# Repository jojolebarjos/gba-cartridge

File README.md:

# GameBoy Advance cartridge

This project is about making homebrew cartridges for the GameBoy Advance, using an FPGA (here a [TinyFPGA](https://tinyfpga.com/) BX).
Given the update frequency (and the fact that both falling-edges and rising-edges are meaningful), this is more convenient than bit-banging using some micro-controller.
A few experiments are available, some making use of an additional micro-controller (here an [Arduino Nano 33 BLE](https://store.arduino.cc/products/arduino-nano-33-ble)) for communication.

## Cartridge protocol

The cartridge has the following pins:

 * 1: `VCC`, at 3.3V.
 * 2: `PHI`, the physical clock, which can be configured (disabled, 4.19MHz, 8.38MHz, 16.78MHz). Disabled by default. See [waitstate control](https://www.akkit.org/info/gbatek.htm#gbasystemcontrol).
 * 3: `~WR`, write control.
 * 4: `~RD`, read control.
 * 5: `~CS`, select ROM.
 * 6-21: `AD`, address and data.
 * 22-29: `A`, address or data.
 * 30: `CS2`, select SRAM.
 * 31: `IRQ`, interrupt request. Can be left unconnected or grounded.
 * 32: `GND`, ground.

General comments about memory accesses:

 * Data format is always little endian, i.e. least significant byte is first.
 * Depending on the requested (virtual) address and operation, the GameBoy will either assume ROM or RAM when accessing the cartridge.
 * ROM data access is 16-bits, hence data is aligned on 2-bytes steps. This means the implicit least-significant bit of the address is always 0 (i.e. `A0..23` is the address divided by 2).
 * ARM instructions (32-bits) are slow to fetch. It is better to use THUMB instructions, or copy the code in WRAM.
 * GamePak accesses can be either sequential or non-sequential. The first access to a random location in ROM must be non-sequential.
 * The GameBoy will wait a few cycles when accessing memory. Up to 3 configurations can be used (useful if the cartridge has multiple ROM units with different physical properties). By default, it will assume 4 cycles for random access, and then 2 cycles for sequential access. See [waitstate control](https://www.akkit.org/info/gbatek.htm#gbasystemcontrol).
 * When doing ROM access, the `AD` bus is used in both direction. The cartridge should actively write only when both `~CS` and `~RD` are low.
 * When doing RAM access, the `AD` bus is used for the 16-bits address, and the 8-bits data is returned through `A16..23`. `~CS2` is used instead of `~CS`.

A read access from the ROM is done as follows:

 * On `~CS` falling-edge, the cartridge latches A0-A23 as address.
 * On `~RD` falling-edge, the cartridge fetches the data at latched address and outputs D0-D15. The output must be ready by next rising-edge of `~RD` (depends on waitstates).
 * On `~RD` rising-edge, the cartridge increments latched address by one (i.e. allow sequential read by just strobing `~RD`).
 * On `~CS` rising-edge, the transaction is done.

While it usually makes no sense to write to a ROM, the GameBoy will submit write commands in a similar fashion, toggling `~WR` instead.
In this project, we use that to let the software write back to the cartridge, for instance to report key input.

Therefore, a simple read-only GamePak ROM does not use `PHI`, `~WR`, `~CS2` and `IRQ`.

Cartridges that require more than 64K of storage will need to use bank switching to map more memory.
This topic has not been investigated in this project.

Relevant links:

 * References
   * https://github.com/gbadev-org/awesome-gbadev
   * https://www.gbadev.org/
   * https://www.akkit.org/info/gbatek.htm
   * https://problemkaputt.de/gbatek.htm
   * http://www.hardwarebook.info/Game_Pak
 * Blogs and websites
   * https://gekkio.fi/
     * https://gekkio.fi/files/gb-docs/gbctr.pdf
     * https://github.com/gekkio/gb-hardware
   * https://www.darkfader.net/gba/
     * http://files.darkfader.net/gba/files/cartridge.txt
   * https://reinerziegler.de.mirrors.gg8.se/GBA/gba.htm
   * http://kylehalladay.com/blog/tutorial/gba/2017/04/18/GBA-By-Example-4.html
   * https://fabiensanglard.net/another_world_polygons_GBA/
   * https://github.com/PeterLemon/GBA
 * Custom cartridges
   * https://github.com/uXeBoy/GBA
   * https://github.com/uXeBoy/GBArduboy
   * http://www.dl9sec.de/prj_gbacart.html
 * Cartridge reader
   * https://www.insidegadgets.com/2011/03/19/gbcartread-arduino-based-gameboy-cart-reader-%E2%80%93-part-1-read-the-rom/
   * https://douevenknow.us/post/68126856498/arduino-based-gba-rom-dumper-part-1
   * https://dragaosemchama.com/en/2015/12/gameboy-pak-reader-cartridge-header/
   * https://mgba.io/2015/10/20/dumping-the-undumped/
 * Multiboot-based
   * https://github.com/Shyri/gba-bt-hid
 * Old GameBoy, but still very interesting
   * https://dhole.github.io/post/gameboy_cartridge_emu_1/
   * https://retrocomputing.stackexchange.com/questions/11732/how-does-the-gameboys-memory-bank-switching-work
   * https://github.com/dwaq/Homebrew-Gameboy-Cartridge
   * https://www.insidegadgets.com/2018/04/18/building-a-2mb-mbc5-gameboy-cart-part-1-cpld-as-the-mbc-and-adding-flash-as-our-rom/
   * http://bitwise.bperki.com/2018/08/08/custom-game-boy-cartridge-project-update-1/
   * https://wiki.tauwasser.eu/view/MBC1
   * https://catskull.net/gameboy-boot-screen-logo.html

## Compiling a GameBoy Advance game

The GameBoy Advance features an ARM-based processor.
We will use [devkitPro](https://devkitpro.org/wiki/Main_Page) to compile binaries.

The most straightforward approach is to use the [Docker image](https://github.com/devkitPro/docker).
We share the local folder with the container, to avoid unnecessary copies.

```
# Run in interactive mode
docker run -ti -v ${PWD}:/rom devkitpro/devkitarm
# On Windows: docker run -ti -v %cd%:/rom devkitpro/devkitarm

# Add compiler binaries to path
export PATH="/opt/devkitpro/devkitARM/bin/:$PATH"

# Go to shared folder and build files
cd /rom/
make
```

Links related to GBA software development:

 * https://www.coranac.com/tonc/text/toc.htm
 * https://devkitpro.org/wiki/Getting_Started
 * https://github.com/devkitPro/docker
 * https://github.com/devkitPro/gba-examples
 * http://kylehalladay.com/blog/tutorial/gba/2017/03/28/GBA-By-Example-1.html
 * https://www.coranac.com/tonc/text/setup.htm#sec-dkp
 * https://www.akkit.org/info/gbatek.htm#gbakeypadinput
 * https://www.coranac.com/tonc/text/keys.htm
 * https://github.com/felixjones/gba-plusplus

Emulators and GameBoy implementations:

 * https://mgba.io/
 * https://github.com/RobertPeip/FPGBA
 * https://github.com/AntonioND/giibiiadvance
 * https://mitxela.com/projects/swotgb/about

## Development PCB

In order to have a flexible playground, a custom-made PCB has been designed using [KiCad](https://www.kicad.org/) and ordered on [JLCPCB](https://jlcpcb.com/).
[This](https://www.aliexpress.com/item/1005003412771520.html) cheap cartridge header can be soldered to connect an actual cartridge, if needed.
A simple casing has been designed using [FreeCAD](https://www.freecadweb.org/) and 3D-printed (resin) to properly fit the GameBoy Advance.
Depending on whether a GameBoy Advance and/or a cartridge is used, the FPGA can have various roles.

 * The 32 pins of the cartridge are forwarded from the GameBoy to the cartridge.
 * Two sets of connectors are available to intercept (or drive) the pins: a 2x16 header for generic usage, and a 2x14 header designed to hold the TinyFPGA BX.
 * A dedicated header is available to configure power supply.
 * `A` is not exposed to the TinyFPGA BX, as there are not enough pins. Note that some GPIO pins are exposed as pads by the FPGA, but this is not convenient for this project.
 * Instead, some pins are exposed as "extra", and can be used either for external communication (e.g. SPI) or connected to `A` to extend the address space.
 * Use ENIG finish (i.e. *not* HASL), for more strength.
 * In order to fit in the opening, a thickness of 0.8mm should be used (as the casing already takes roughly 1mm).

See the [schema](pcb.sch.pdf) for more details.

## Getting started with TinyFPGA BX

As described in the [User Guide](https://tinyfpga.com/bx/guide.html), install [APIO](https://github.com/FPGAWARS/apio):

```
conda create -n fpga python=3.7
activate fpga
pip install apio==0.4.0b5 tinyprog
apio install system scons icestorm iverilog
```

Connect the board and run:

```
apio install drivers
apio drivers --serial-enable
```

Reconnect the board, and check that the device is recognized.
Windows might take a few seconds to actually detect and properly setup the serial device.

```
apio system --lsserial
```

Make sure the board is up-to-date:

```
tinyprog --update-bootloader
```

For better integration, use [Atom](https://atom.io/) and install the `apio-ide` package.
Note that you should run Atom inside the Conda environment, so that paths are properly set up:

```
atom --new-instance
```

Using the [default template](https://github.com/tinyfpga/TinyFPGA-BX/tree/master/apio_template), you can quickly start developing the TinyFPGA.

Note that you can upload the code by calling `tinyprog` directly:

```
tinyprog --program hardware.bin
```

The `apio-ide` package provide shortcuts for the most common operations, i.e. build and program.
Use `F8` to show the compilation log after a successful build.

Links:

 * https://tinyfpga.com/
 * http://www.clifford.at/icestorm/
 * https://www.youtube.com/watch?v=ZNunxg7o8l0
 * https://hackaday.io/project/159191-fpga-bootcamp-1
 * https://github.com/YosysHQ/nextpnr

## Experiments

A few simple experiments have been made until now.

### Cartridge dump

An Arduino Nano 33 BLE is connected to a TinyFPGA BX over SPI.

| Name | Arduino Nano 33 BLE | Wire | Board | TinyFPGA BX |
| ---- | ---- | ---- | ---- | ---- |
| GND | GND | black | GND | GND | GND |
| MISO | D2 (2) | green | EXT0 | 1 (A2) |
| MOSI | D3 (3) | blue | EXT1 | 2 (A1) |
| SCK | D4 (4) | white | EXT2 | 3 (B1) |
| SS | D5 (5) | yellow | EXT3 | 4 (C2) |

The cartridge is powered by the TinyFPGA BX, i.e. `VCC_CART` is connected to `VOUT`.

This is a naive implementation of the above-mentioned protocol:

 * The FPGA toggles `~CS` and `~RD`, writes the address and reads the output through `AD`. Note that, as `A` is ignored, only the first 131072 can be read.
 * The Arduino acts as a bridge, communicating with the FPGA using SPI and with the computer using USB.
 * A Python script sends the commands and dumps the content to a binary file.

Note that this approach does not handle any memory bank.
Therefore, it cannot be used as-is to dump a whole cartridge.

See [`./experiments/dump/`](./dump/) for more details.

### Read-only cartridge

The TinyFPGA BX acts as a read-only ROM cartridge.
A simple "game" is provided, where a white dot is moved using the arrows.

See [`./experiments/read/`](./read/) for more details.

### Read-write

The TinyFPGA BX acts as a writable ROM cartridge.
A simple "game" is provided, where buttons are written at each frame to the cartridge memory.

See [`./experiments/write/`](./write/) for more details.

### USB gamepad

The TinyFPGA BX acts as a writable ROM cartridge.
A simple "game" is provided, where buttons are written at each frame to the cartridge memory.
This information is then forwarded to an Arduino Nano 33 BLE, which is recognized as a HID gamepad.

TODO: use HID over USB/BLE

TODO: use interrupts on GBA (and sleep when no button is pressed)

TODO: make FPGA the SPI master, or use interrupts to let the Arduino communicate only when needed

See [`./experiments/gamepad/`](./gamepad/) for more details.

### Direct Memory Access

...

http://problemkaputt.de/gbatek-gba-dma-transfers.htm
https://gbdev.gg8.se/wiki/articles/Video_Display
https://austinjadams.com/blog/autograding-gba-dma/
https://badd10de.dev/notes/gba-programming.html

See [`./experiments/dma/`](./dma/) for more details.

### VGA

The GBA has a TFT color LCD that is 240 x 160 pixels in size and has a refresh rate of exactly 280896 cpu cycles per frame, or around 59.73 hz.
Most GBA programs will need to structure themselves around this refresh rate.
The LCD can display 15-bit RGB colors (0bxbbbbbgggggrrrrr).

TODO:
 * Use backbuffer (with palette) mode 4, to acquire next frame during previous one is drawn
 * VGA is an analog signal, with 5 (+GND) relevant pins: R, G, B, H-Sync, V-Sync
 * We can naively connect these to digital inputs, effectively displaying only 8 colors
 * We can also use an analog-to-digital serial converter, if FPGA is fast enough
 * https://electronics.stackexchange.com/questions/134674/how-vga-monitor-detects-video-resolution
 * Need 3:2 resolution, so maybe use 320x200 and trim 20 pixels horizontally? https://www.videotechnology.com/0904/formats.html

The closest standard mode is 720x480 @60Hz RGB 4:4:4

 * https://en.wikipedia.org/wiki/Video_Graphics_Array
 * https://en.wikipedia.org/wiki/HDMI
 * https://www.youtube.com/watch?v=l7rce6IQDWs&ab_channel=BenEater
 * http://tinyvga.com/vga-timing
 * https://ez.analog.com/cfs-file/__key/telligent-evolution-components-attachments/00-317-00-00-00-05-21-37/HDMISpecification13a.pdf
 * https://forum.digikey.com/t/vga-controller-vhdl/12794

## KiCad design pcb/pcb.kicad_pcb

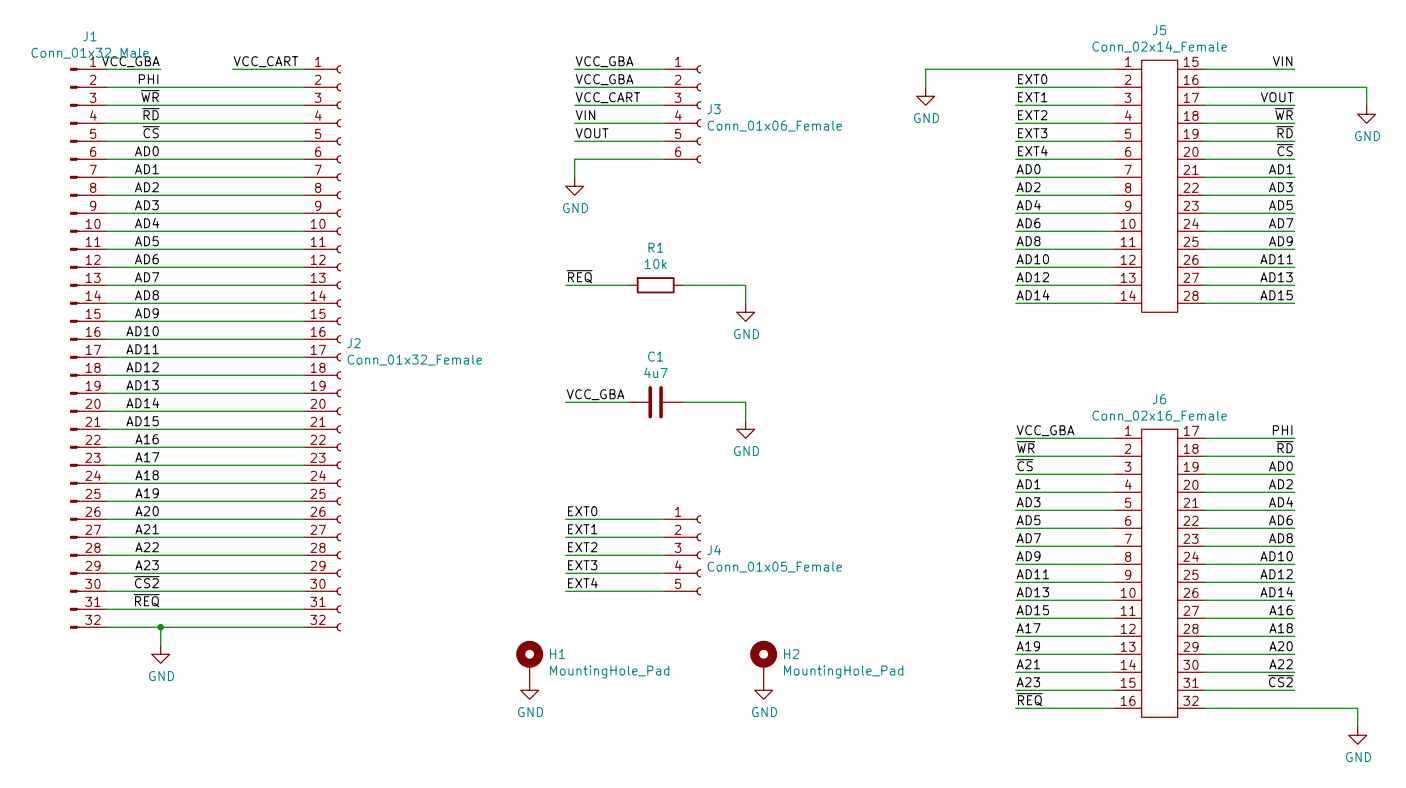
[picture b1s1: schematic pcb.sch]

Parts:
C1: 4u7; C_0805_2012Metric_Pad1.15x1.40mm_HandSolder
H1, H2: MountingHole_Pad; MountingHole_3.2mm_M3_Pad
J1: Conn_01x32_Male; GBA
J2: Conn_01x32_Female; CART
J3: Conn_01x06_Female; PinHeader_Power
J4: Conn_01x05_Female; PinHeader_Extra
J5: Conn_02x14_Female; PinHeader_TinyFPGA_BX
J6: Conn_02x16_Female; PinHeader_Secondary
R1: 10k; R_0805_2012Metric_Pad1.15x1.40mm_HandSolder

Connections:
/A16: J1.22, J2.22, J6.27
/A17: J1.23, J2.23, J6.12
/A18: J1.24, J2.24, J6.28
/A19: J1.25, J2.25, J6.13
/A20: J1.26, J2.26, J6.29
/A21: J1.27, J2.27, J6.14
/A22: J1.28, J2.28, J6.30
/A23: J1.29, J2.29, J6.15
/AD0: J1.6, J2.6, J5.7, J6.19
/AD1: J1.7, J2.7, J5.21, J6.4
/AD2: J1.8, J2.8, J5.8, J6.20
/AD3: J1.9, J2.9, J5.22, J6.5
/AD4: J1.10, J2.10, J5.9, J6.21
/AD5: J1.11, J2.11, J5.23, J6.6
/AD6: J1.12, J2.12, J5.10, J6.22
/AD7: J1.13, J2.13, J5.24, J6.7
/AD8: J1.14, J2.14, J5.11, J6.23
/AD9: J1.15, J2.15, J5.25, J6.8
/AD10: J1.16, J2.16, J5.12, J6.24
/AD11: J1.17, J2.17, J5.26, J6.9
/AD12: J1.18, J2.18, J5.13, J6.25
/AD13: J1.19, J2.19, J5.27, J6.10
/AD14: J1.20, J2.20, J5.14, J6.26
/AD15: J1.21, J2.21, J5.28, J6.11
/EXT0: J4.1, J5.2
/EXT1: J4.2, J5.3
/EXT2: J4.3, J5.4
/EXT3: J4.4, J5.5
/EXT4: J4.5, J5.6
/PHI: J1.2, J2.2, J6.17
/VCC_CART: J2.1, J3.3
/VCC_GBA: C1.2, J1.1, J3.1, J3.2, J6.1
/VIN: J3.4, J5.15
/VOUT: J3.5, J5.17
/~CS: J1.5, J2.5, J5.20, J6.3
/~CS2: J1.30, J2.30, J6.31
/~RD: J1.4, J2.4, J5.19, J6.18
/~REQ: J1.31, J2.31, J6.16, R1.2
/~WR: J1.3, J2.3, J5.18, J6.2
GND: C1.1, H1.1, H2.1, J1.32, J2.32, J3.6, J5.1, J5.16, J6.32, R1.1

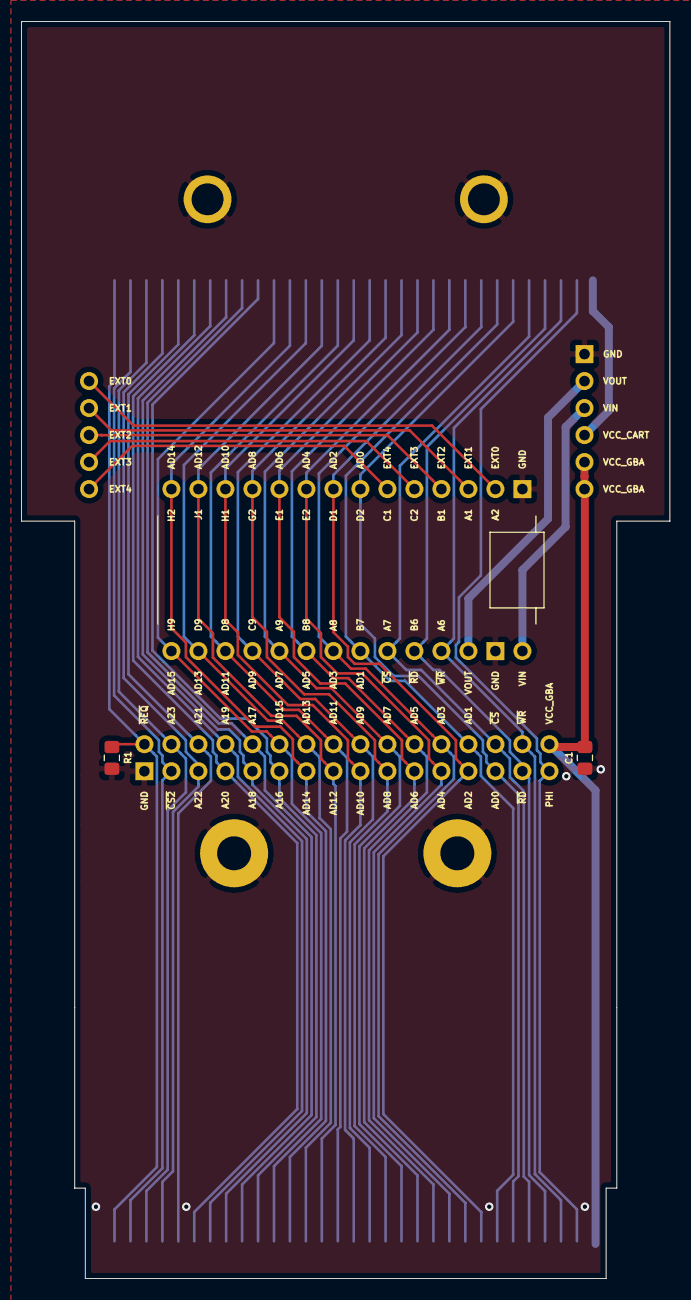
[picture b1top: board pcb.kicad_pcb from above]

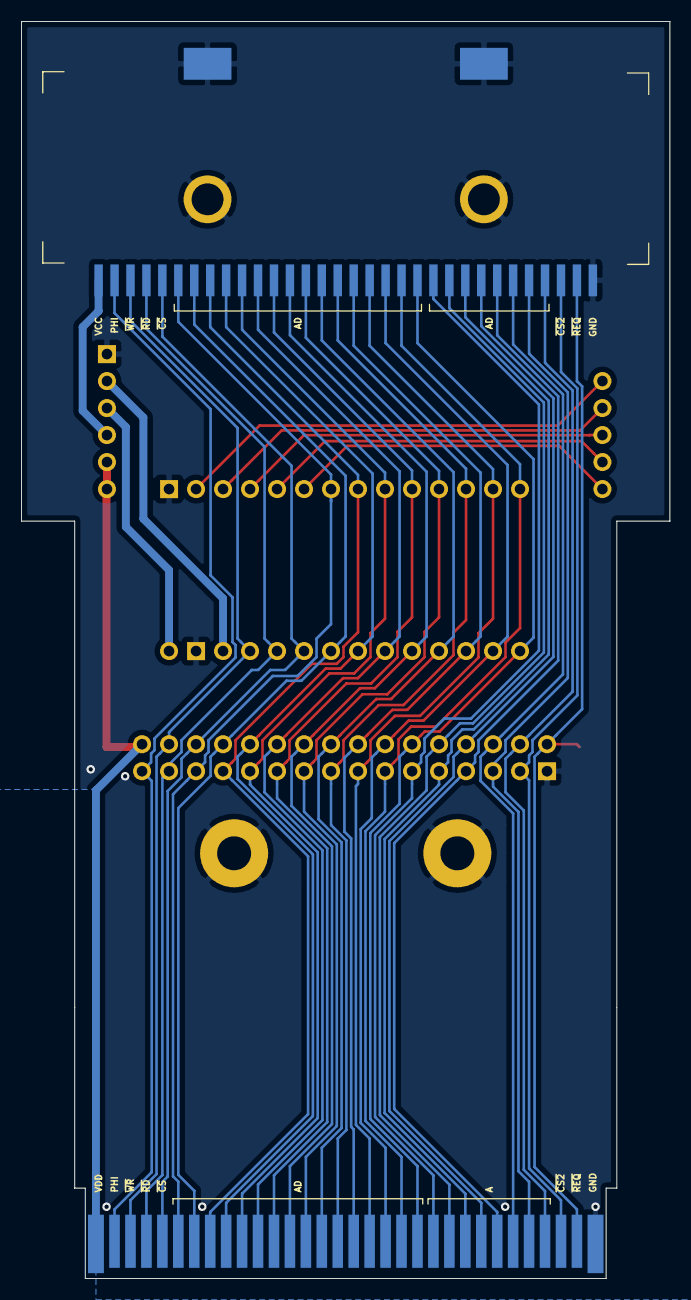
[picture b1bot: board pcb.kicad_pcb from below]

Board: 2 copper layers, 61.0 x 118.2 mm, 10 parts (2 on the bottom side), 40 nets.

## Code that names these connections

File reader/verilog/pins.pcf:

###############################################################################
#
# TinyFPGA BX constraint file (.pcf)
#
###############################################################################
#
# Copyright (c) 2018, Luke Valenty
# All rights reserved.
#
# Redistribution and use in source and binary forms, with or without
# modification, are permitted provided that the following conditions are met:
#
# 1. Redistributions of source code must retain the above copyright notice, this
#    list of conditions and the following disclaimer.
# 2. Redistributions in binary form must reproduce the above copyright notice,
#    this list of conditions and the following disclaimer in the documentation
#    and/or other materials provided with the distribution.
#
# THIS SOFTWARE IS PROVIDED BY THE COPYRIGHT HOLDERS AND CONTRIBUTORS "AS IS" AND
# ANY EXPRESS OR IMPLIED WARRANTIES, INCLUDING, BUT NOT LIMITED TO, THE IMPLIED
# WARRANTIES OF MERCHANTABILITY AND FITNESS FOR A PARTICULAR PURPOSE ARE
# DISCLAIMED. IN NO EVENT SHALL THE COPYRIGHT OWNER OR CONTRIBUTORS BE LIABLE FOR
# ANY DIRECT, INDIRECT, INCIDENTAL, SPECIAL, EXEMPLARY, OR CONSEQUENTIAL DAMAGES
# (INCLUDING, BUT NOT LIMITED TO, PROCUREMENT OF SUBSTITUTE GOODS OR SERVICES;
# LOSS OF USE, DATA, OR PROFITS; OR BUSINESS INTERRUPTION) HOWEVER CAUSED AND
# ON ANY THEORY OF LIABILITY, WHETHER IN CONTRACT, STRICT LIABILITY, OR TORT
# (INCLUDING NEGLIGENCE OR OTHERWISE) ARISING IN ANY WAY OUT OF THE USE OF THIS
# SOFTWARE, EVEN IF ADVISED OF THE POSSIBILITY OF SUCH DAMAGE.
#
# The views and conclusions contained in the software and documentation are those
# of the authors and should not be interpreted as representing official policies,
# either expressed or implied, of the <project name> project.
#
###############################################################################

####
# TinyFPGA BX information: https://github.com/tinyfpga/TinyFPGA-BX/
####

# Left side of board
set_io --warn-no-port PIN_1 A2
set_io --warn-no-port PIN_2 A1
set_io --warn-no-port PIN_3 B1
set_io --warn-no-port PIN_4 C2
set_io --warn-no-port PIN_5 C1
set_io --warn-no-port PIN_6 D2
set_io --warn-no-port PIN_7 D1
set_io --warn-no-port PIN_8 E2
set_io --warn-no-port PIN_9 E1
set_io --warn-no-port PIN_10 G2
set_io --warn-no-port PIN_11 H1
set_io --warn-no-port PIN_12 J1
set_io --warn-no-port PIN_13 H2

# Right side of board
set_io --warn-no-port PIN_14 H9
set_io --warn-no-port PIN_15 D9
set_io --warn-no-port PIN_16 D8
set_io --warn-no-port PIN_17 C9
set_io --warn-no-port PIN_18 A9
set_io --warn-no-port PIN_19 B8
set_io --warn-no-port PIN_20 A8
set_io --warn-no-port PIN_21 B7
set_io --warn-no-port PIN_22 A7
set_io --warn-no-port PIN_23 B6
set_io --warn-no-port PIN_24 A6

# SPI flash interface on bottom of board
set_io --warn-no-port SPI_SS F7
set_io --warn-no-port SPI_SCK G7
set_io --warn-no-port SPI_IO0 G6
set_io --warn-no-port SPI_IO1 H7
set_io --warn-no-port SPI_IO2 H4
set_io --warn-no-port SPI_IO3 J8

# General purpose pins on bottom of board
set_io --warn-no-port PIN_25 G1
set_io --warn-no-port PIN_26 J3
set_io --warn-no-port PIN_27 J4
set_io --warn-no-port PIN_28 G9
set_io --warn-no-port PIN_29 J9
set_io --warn-no-port PIN_30 E8
set_io --warn-no-port PIN_31 J2

# LED
set_io --warn-no-port LED B3

# USB
set_io --warn-no-port USBP B4
set_io --warn-no-port USBN A4
set_io --warn-no-port USBPU A3

# 16MHz clock
set_io --warn-no-port CLK B2 # input

# Cartridge
set_io --warn-no-port AD[0] D2 # PIN_6
set_io --warn-no-port AD[2] D1 # PIN_7
set_io --warn-no-port AD[4] E2 # PIN_8
set_io --warn-no-port AD[6] E1 # PIN_9
set_io --warn-no-port AD[8] G2 # PIN_10
set_io --warn-no-port AD[10] H1 # PIN_11
set_io --warn-no-port AD[12] J1 # PIN_12
set_io --warn-no-port AD[14] H2 # PIN_13
set_io --warn-no-port AD[15] H9 # PIN_14
set_io --warn-no-port AD[13] D9 # PIN_15
set_io --warn-no-port AD[11] D8 # PIN_16
set_io --warn-no-port AD[9] C9 # PIN_17
set_io --warn-no-port AD[7] A9 # PIN_18
set_io --warn-no-port AD[5] B8 # PIN_19
set_io --warn-no-port AD[3] A8 # PIN_20
set_io --warn-no-port AD[1] B7 # PIN_21
set_io --warn-no-port CS A7 # PIN_22
set_io --warn-no-port RD B6 # PIN_23
set_io --warn-no-port WR A6 # PIN_24

# SPI
set_io --warn-no-port MISO A2 # PIN_1 -> EXT0
set_io --warn-no-port MOSI A1 # PIN_2 -> EXT1
set_io --warn-no-port SCK B1 # PIN_3 -> EXT2
set_io --warn-no-port SS C2 # PIN_4 -> EXT3

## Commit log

2022-01-24 Add early draft
2022-01-27 Move headers to the other side
2022-04-18 Toward SPI-based cartridge reader
2022-04-18 Add working version of dump (although, slow)
2022-04-18 Add some documentation
2022-04-19 Add minimalist ROM cartridge in Verilog
2022-04-19 Push latest version
2022-04-19 Add Gerber files
2022-04-19 Add 3D casing model
2022-04-19 Refactor and document a bit
2022-04-19 Fix a few typos
2022-04-19 Add license
2022-04-19 Small fixes
2022-04-20 Add gamepad draft
2022-04-28 Toward HDMI experiment
2022-04-29 Refactor experiments
2022-05-08 Rename folders
2022-05-10 Add gamepad experiment (active-polling)
